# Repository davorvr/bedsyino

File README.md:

# BeDSyino

#### What is it?

The **[BeDSy (Behaviour-recording Device Synchroniser)](https://github.com/davorvr/bedsy)** is a platform for hardware triggering and synchronisation of equipment for laboratory animal behavioural monitoring. For more information about the BeDSy platform, check the **[BeDSy repository](https://github.com/davorvr/bedsy)**.

The platform consists of two components: the **[BeDSy Python package](https://github.com/davorvr/bedsy)**, which interfaces with the **BeDSyino**, a hardware platform which sends custom trigger signals to animal behaviour-monitoring devices.

The BeDSyino is based on the [Teensy 4.0](https://www.pjrc.com/store/teensy40.html) platform (with plans to migrate to the Teensy 4.1) and [Teensyduino](https://www.pjrc.com/teensy/teensyduino.html).

#### Current state

The [BeDSyino](https://github.com/davorvr/bedsyino) is still cooking. While the code is mostly complete, only a single hand-soldered, protoboard-based prototype has been developed thus far. A modular, extensible hardware platform is currently in the works and hardware files will be uploaded as soon as it's ready. The `.ino` file contains a lot of (hopefully) helpful comments, but more work on the documentation is necessary.

*TO DO - expand*

#### License

The code is distributed under GPLv3.

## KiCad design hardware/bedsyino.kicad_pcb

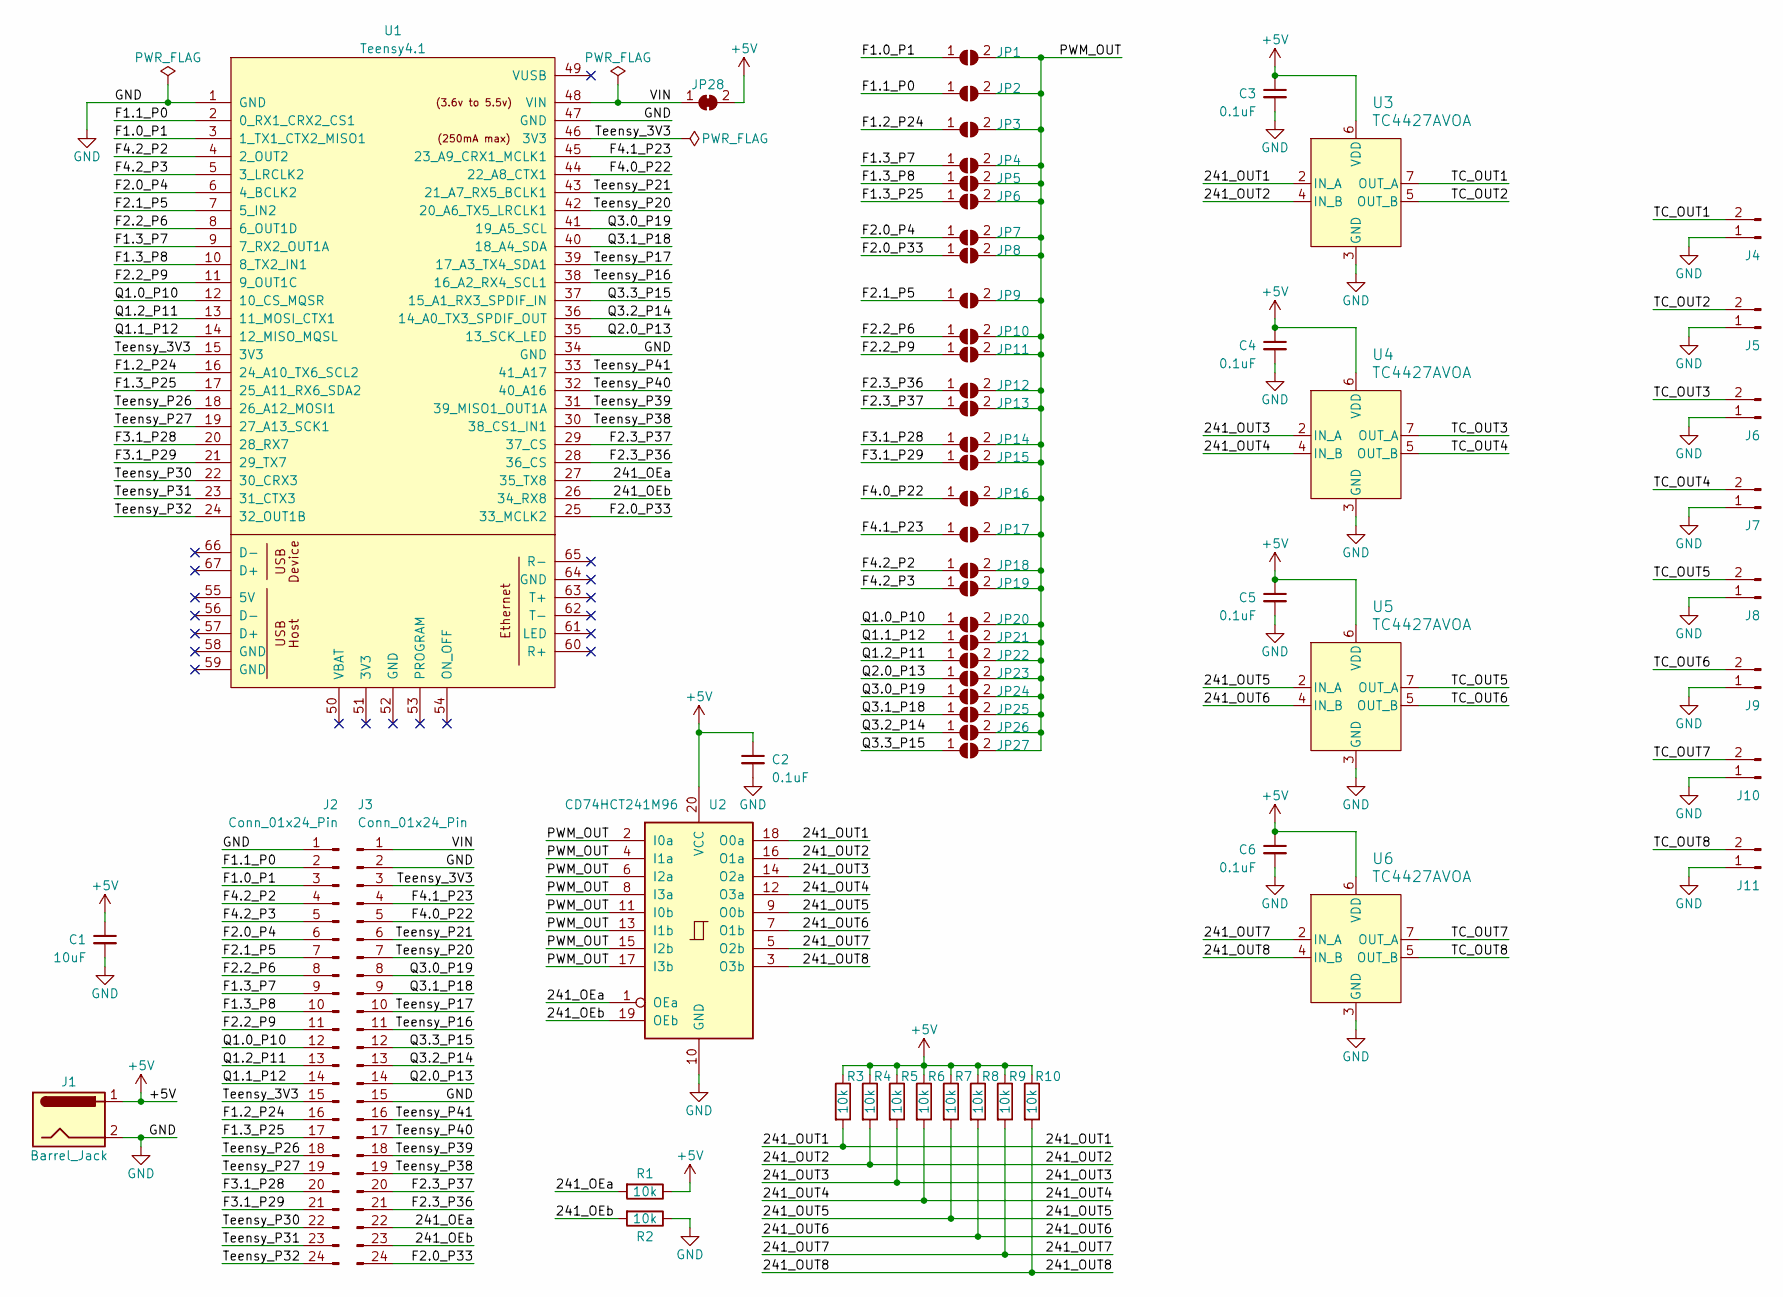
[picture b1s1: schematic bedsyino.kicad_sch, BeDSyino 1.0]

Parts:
C1: 10uF; C_1206_3216Metric; LCSC Part # C97954
C2, C3, C4, C5, C6: 0.1uF; C_0805_2012Metric; LCSC Part # C49678
J1: Barrel_Jack; BarrelJack_Horizontal
J2, J3: Conn_01x24_Pin; PinHeader_1x24_P2.54mm_Vertical
J4, J5, J6, J7, J8, J9, J10, J11: Conn_01x02_Pin; Molex_KK-254_AE-7395-02_1x02_P2.54mm_Horizontal
JP1: F1.0 P1; SolderJumper-2_P1.3mm_Open_TrianglePad1.0x1.5mm
JP2: F1.1 P0; SolderJumper-2_P1.3mm_Open_TrianglePad1.0x1.5mm
JP3: F1.2 P24; SolderJumper-2_P1.3mm_Open_TrianglePad1.0x1.5mm
JP4: F1.3 P7; SolderJumper-2_P1.3mm_Open_TrianglePad1.0x1.5mm
JP5: F1.3 P8; SolderJumper-2_P1.3mm_Open_TrianglePad1.0x1.5mm
JP6: F1.3 P25; SolderJumper-2_P1.3mm_Open_TrianglePad1.0x1.5mm
JP7: F2.0 P4; SolderJumper-2_P1.3mm_Open_TrianglePad1.0x1.5mm
JP8: F2.0 P33; SolderJumper-2_P1.3mm_Open_TrianglePad1.0x1.5mm
JP9: F2.1 P5; SolderJumper-2_P1.3mm_Open_TrianglePad1.0x1.5mm
JP10: F2.2 P6; SolderJumper-2_P1.3mm_Open_TrianglePad1.0x1.5mm
JP11: F2.2 P9; SolderJumper-2_P1.3mm_Open_TrianglePad1.0x1.5mm
JP12: F2.3 P36; SolderJumper-2_P1.3mm_Open_TrianglePad1.0x1.5mm
JP13: F2.3 P37; SolderJumper-2_P1.3mm_Open_TrianglePad1.0x1.5mm
JP14: F3.1 P28; SolderJumper-2_P1.3mm_Open_TrianglePad1.0x1.5mm
JP15: F3.1 P29; SolderJumper-2_P1.3mm_Open_TrianglePad1.0x1.5mm
JP16: F4.0 P22; SolderJumper-2_P1.3mm_Open_TrianglePad1.0x1.5mm
JP17: F4.1 P23; SolderJumper-2_P1.3mm_Open_TrianglePad1.0x1.5mm
JP18: F4.2 P2; SolderJumper-2_P1.3mm_Open_TrianglePad1.0x1.5mm
JP19: F4.2 P3; SolderJumper-2_P1.3mm_Open_TrianglePad1.0x1.5mm
JP20: Q1.0 P10; SolderJumper-2_P1.3mm_Open_TrianglePad1.0x1.5mm
JP21: Q1.1 P12; SolderJumper-2_P1.3mm_Open_TrianglePad1.0x1.5mm
JP22: Q1.2 P11; SolderJumper-2_P1.3mm_Open_TrianglePad1.0x1.5mm
JP23: Q2.0 P13; SolderJumper-2_P1.3mm_Open_TrianglePad1.0x1.5mm
JP24: Q3.0 P19; SolderJumper-2_P1.3mm_Open_TrianglePad1.0x1.5mm
JP25: Q3.1 P18; SolderJumper-2_P1.3mm_Open_TrianglePad1.0x1.5mm
JP26: Q3.2 P14; SolderJumper-2_P1.3mm_Open_TrianglePad1.0x1.5mm
JP27: Q3.3 P15; SolderJumper-2_P1.3mm_Open_TrianglePad1.0x1.5mm
JP28: PWR SELECT; SolderJumper-2_P1.3mm_Bridged2Bar_Pad1.0x1.5mm
R1, R2, R3, R4, R5, R6, R7, R8, R9, R10: 10k; R_0805_2012Metric; LCSC Part # C100047
U1: Teensy4.1; Teensy41
U2: CD74HCT241M96; SOIC-20W_7.5x12.8mm_P1.27mm; LCSC Part # C2860724
U3, U4, U5, U6: TC4427AVOA; SOIC8-N_MC_MCH; LCSC Part # C624944

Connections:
+5V: C1.1, C2.1, C3.1, C4.1, C5.1, C6.1, J1.1, JP28.2 (B), R1.1, R3.1, R4.1, R5.1, R6.1, R7.1, R8.1, R9.1, R10.1, U2.20 (VCC), U3.6 (VDD), U4.6 (VDD), U5.6 (VDD), U6.6 (VDD)
/241_OEa: J3.22, R1.2, U1.27 (35_TX8), U2.1 (OEa)
/241_OEb: J3.23, R2.2, U1.26 (34_RX8), U2.19 (OEb)
/241_OUT1: R3.2, U2.18 (O0a), U3.2 (IN_A)
/241_OUT2: R4.2, U2.16 (O1a), U3.4 (IN_B)
/241_OUT3: R5.2, U2.14 (O2a), U4.2 (IN_A)
/241_OUT4: R6.2, U2.12 (O3a), U4.4 (IN_B)
/241_OUT5: R7.2, U2.9 (O0b), U5.2 (IN_A)
/241_OUT6: R8.2, U2.7 (O1b), U5.4 (IN_B)
/241_OUT7: R9.2, U2.5 (O2b), U6.2 (IN_A)
/241_OUT8: R10.2, U2.3 (O3b), U6.4 (IN_B)
/F1.0_P1: J2.3, JP1.1 (A), U1.3 (1_TX1_CTX2_MISO1)
/F1.1_P0: J2.2, JP2.1 (A), U1.2 (0_RX1_CRX2_CS1)
/F1.2_P24: J2.16, JP3.1 (A), U1.16 (24_A10_TX6_SCL2)
/F1.3_P7: J2.9, JP4.1 (A), U1.9 (7_RX2_OUT1A)
/F1.3_P8: J2.10, JP5.1 (A), U1.10 (8_TX2_IN1)
/F1.3_P25: J2.17, JP6.1 (A), U1.17 (25_A11_RX6_SDA2)
/F2.0_P4: J2.6, JP7.1 (A), U1.6 (4_BCLK2)
/F2.0_P33: J3.24, JP8.1 (A), U1.25 (33_MCLK2)
/F2.1_P5: J2.7, JP9.1 (A), U1.7 (5_IN2)
/F2.2_P6: J2.8, JP10.1 (A), U1.8 (6_OUT1D)
/F2.2_P9: J2.11, JP11.1 (A), U1.11 (9_OUT1C)
/F2.3_P36: J3.21, JP12.1 (A), U1.28 (36_CS)
/F2.3_P37: J3.20, JP13.1 (A), U1.29 (37_CS)
/F3.1_P28: J2.20, JP14.1 (A), U1.20 (28_RX7)
/F3.1_P29: J2.21, JP15.1 (A), U1.21 (29_TX7)
/F4.0_P22: J3.5, JP16.1 (A), U1.44 (22_A8_CTX1)
/F4.1_P23: J3.4, JP17.1 (A), U1.45 (23_A9_CRX1_MCLK1)
/F4.2_P2: J2.4, JP18.1 (A), U1.4 (2_OUT2)
/F4.2_P3: J2.5, JP19.1 (A), U1.5 (3_LRCLK2)
/PWM_OUT: JP1.2 (B), JP2.2 (B), JP3.2 (B), JP4.2 (B), JP5.2 (B), JP6.2 (B), JP7.2 (B), JP8.2 (B), JP9.2 (B), JP10.2 (B), JP11.2 (B), JP12.2 (B), JP13.2 (B), JP14.2 (B), JP15.2 (B), JP16.2 (B), JP17.2 (B), JP18.2 (B), JP19.2 (B), JP20.2 (B), JP21.2 (B), JP22.2 (B), JP23.2 (B), JP24.2 (B), JP25.2 (B), JP26.2 (B), JP27.2 (B), U2.2 (I0a), U2.4 (I1a), U2.6 (I2a), U2.8 (I3a), U2.11 (I0b), U2.13 (I1b), U2.15 (I2b), U2.17 (I3b)
/Q1.0_P10: J2.12, JP20.1 (A), U1.12 (10_CS_MQSR)
/Q1.1_P12: J2.14, JP21.1 (A), U1.14 (12_MISO_MQSL)
/Q1.2_P11: J2.13, JP22.1 (A), U1.13 (11_MOSI_CTX1)
/Q2.0_P13: J3.14, JP23.1 (A), U1.35 (13_SCK_LED)
/Q3.0_P19: J3.8, JP24.1 (A), U1.41 (19_A5_SCL)
/Q3.1_P18: J3.9, JP25.1 (A), U1.40 (18_A4_SDA)
/Q3.2_P14: J3.13, JP26.1 (A), U1.36 (14_A0_TX3_SPDIF_OUT)
/Q3.3_P15: J3.12, JP27.1 (A), U1.37 (15_A1_RX3_SPDIF_IN)
/TC_OUT1: J4.2, U3.7 (OUT_A)
/TC_OUT2: J5.2, U3.5 (OUT_B)
/TC_OUT3: J6.2, U4.7 (OUT_A)
/TC_OUT4: J7.2, U4.5 (OUT_B)
/TC_OUT5: J8.2, U5.7 (OUT_A)
/TC_OUT6: J9.2, U5.5 (OUT_B)
/TC_OUT7: J10.2, U6.7 (OUT_A)
/TC_OUT8: J11.2, U6.5 (OUT_B)
/Teensy_3V3: J2.15, J3.3, U1.15 (3V3), U1.46 (3V3)
/Teensy_P16: J3.11, U1.38 (16_A2_RX4_SCL1)
/Teensy_P17: J3.10, U1.39 (17_A3_TX4_SDA1)
/Teensy_P20: J3.7, U1.42 (20_A6_TX5_LRCLK1)
/Teensy_P21: J3.6, U1.43 (21_A7_RX5_BCLK1)
/Teensy_P26: J2.18, U1.18 (26_A12_MOSI1)
/Teensy_P27: J2.19, U1.19 (27_A13_SCK1)
/Teensy_P30: J2.22, U1.22 (30_CRX3)
/Teensy_P31: J2.23, U1.23 (31_CTX3)
/Teensy_P32: J2.24, U1.24 (32_OUT1B)
/Teensy_P38: J3.19, U1.30 (38_CS1_IN1)
/Teensy_P39: J3.18, U1.31 (39_MISO1_OUT1A)
/Teensy_P40: J3.17, U1.32 (40_A16)
/Teensy_P41: J3.16, U1.33 (41_A17)
/VIN: J3.1, JP28.1 (A), U1.48 (VIN)
GND: C1.2, C2.2, C3.2, C4.2, C5.2, C6.2, J1.2, J2.1, J3.2, J3.15, J4.1, J5.1, J6.1, J7.1, J8.1, J9.1, J10.1, J11.1, R2.1, U1.1 (GND), U1.34 (GND), U1.47 (GND), U2.10 (GND), U3.3 (GND), U4.3 (GND), U5.3 (GND), U6.3 (GND)

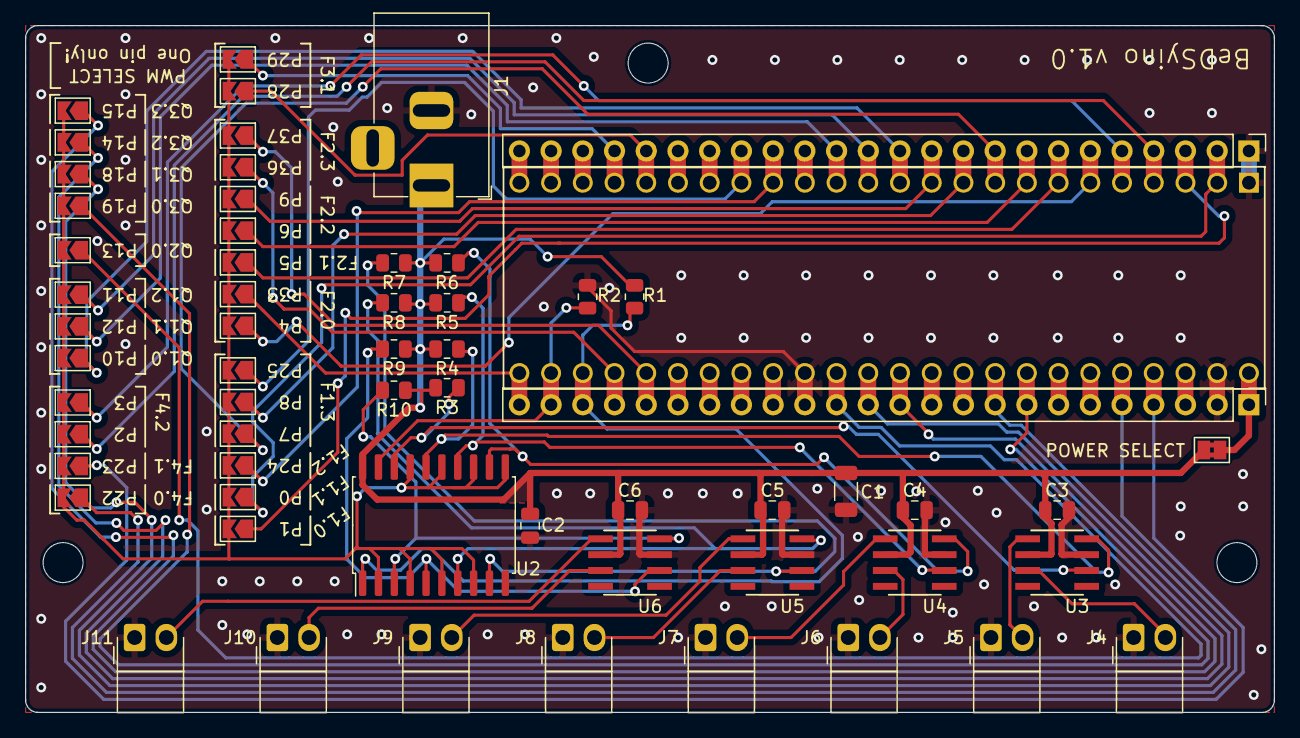
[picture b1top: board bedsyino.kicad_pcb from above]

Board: 2 copper layers, 100.0 x 55.0 mm, 61 parts (0 on the bottom side), 63 nets.

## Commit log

2024-02-13 added PCB design for v1.0
2024-02-13 Updated code for Bedsyino v1.0 test
    Code still specific for one use case, main block comment still not updated
